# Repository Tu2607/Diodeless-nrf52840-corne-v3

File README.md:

# Diodeless nRF52840 Corne v3

A diodeless (direct-pin), Bluetooth variant of the [Corne Cherry v3.0.1](https://github.com/foostan/crkbd/tree/v3-final) by foostan. This repository holds the files and instructions needed to build one.

**Status: revision 0.4. The board passes KiCad DRC for connectivity and clearance, but it has not been fabricated or tested yet. Read [Check before ordering](#check-before-ordering) first.**

## What it is

- 3x6+3 keys per half, with the same outline, key positions and mounting holes as Corne v3
- nice!nano v2 (nRF52840) running ZMK, one per half
- One GPIO per switch and no diodes. All 21 GPIOs per half are used, including the three inner pads P1.01, P1.02 and P1.07
- Every key takes either a Kailh MX hotswap socket or a Kailh Choc v1 hotswap socket
- C&K GT11MSCBE sealed toggle as the power switch, where the Corne's TRRS jack was
- No OLED, no RGB and no TRRS cable

## 3D preview

These are renders of a 3D model built from the board file. Part positions and sizes are real, but the parts are simple block models and the socket heights are typical values, not measured.

For a model you can spin around, download [`3d-viewer.html`](3d-viewer.html) and open it in a browser. It needs an internet connection the first time, to load the 3D library.

The underside, with MX hotswap sockets on one half and Choc sockets on the other for comparison. A real build uses one type per key.

| MX sockets | Choc sockets |
|---|---|
|  |  |

## Files

| Path | Contents |
|---|---|
| `gerbers/corne-diodeless-gerbers.zip` | The file to upload to a PCB manufacturer |
| `gerbers/` | The same gerber and drill files, unzipped |
| `pcb/` | KiCad 7 board, project file and footprint library, for viewing or editing |
| `BOM.md` | Parts list with part numbers and quantities |
| `PINMAP.md` | Which pin each key uses |
| `boards/`, `config/`, `build.yaml`, `zephyr/` | ZMK firmware source. See [Firmware](#firmware) |
| `images/` | Board renders and 3D previews |
| `3d-viewer.html` | Interactive 3D model. Download it and open it in a browser |

There is no schematic. Each switch simply connects one controller pin to ground, as listed in `PINMAP.md`.

## Check before ordering

- **Power switch rating.** The GT11MSCBE is rated 0.4 VA at up to 20 V, about 95 mA at battery voltage. The nice!nano charges at about 100 mA through the switch, so the switch is at its limit while charging.
- **Inner controller pads.** The position of P1.01, P1.02 and P1.07 comes from community footprints. Check it against a real nice!nano on the 1:1 print.
- **Battery polarity.** JST-PH battery leads are not standardised. Match your battery's red wire to the + mark on the board.
- **Plates and cases.** Corne v3 plates and cases are cut for MX switches. A Choc build needs a Choc plate or no plate.

## Parts

The full parts list with part numbers and quantities is in [`BOM.md`](BOM.md).

## Ordering the PCB

Upload `gerbers/corne-diodeless-gerbers.zip`. It is a two-layer board, 1.6 mm thick. The file is a panel that holds both halves, so some manufacturers will price it as more than one design.

## Assembly

1. **Break the halves out** of the frame and file the tab edges smooth.
2. **Hotswap sockets, on the back.** Each key has two pairs of pads: the MX pair on one side of the switch centre and the Choc pair on the other. Solder sockets to one pair only. See the picture below.
3. **Power switch, on the top.** Solder the GT11MSCBE to the pads marked PWR at the inner edge. The three pads on one side are the contacts and the two on the other side hold it down. The pads match the land pattern in the C&K GT series datasheet (0.76 x 3.17 mm pads at 2.54 mm pitch, 8.38 mm across). The lever throws toward and away from the board edge.
4. **Reset button, on the top**, at the pads marked RESET.
5. **Battery connector, on the top**, at the pads marked BAT. Skip this if you will solder the battery leads straight to the pads.
6. **Controller sockets, on the top.** Fit the two 12-pin rows, and the three single sockets in the holes marked 107, 102 and 101.
7. **Controller.** Solder pins to the nice!nano, including the three inner pads, and plug it in face down, with the components toward the PCB and the USB port at the top edge.
8. **Battery.** With the power switch off, connect the battery, checking + and -.
9. **Switches and keycaps.**

### Using a different power switch

Two holes marked TOGGLE sit next to the power switch and are wired in parallel with it. To use an off-board switch, leave the PWR pads empty and wire your switch across those two holes.

## Firmware

The board runs [ZMK](https://zmk.dev). A stock Corne firmware will not work, because this board has no key matrix. This repo carries its own ZMK setup:

| Path | Contents |
|---|---|
| `boards/shields/corne_diodeless/` | The board definition: one pin per key for each half |
| `config/corne_diodeless.keymap` | The keymap. It starts as a copy of the stock ZMK Corne keymap |
| `config/corne_diodeless.conf` | Firmware settings |
| `build.yaml` | The list of firmware files to build |

### Getting the firmware

GitHub builds the firmware whenever the firmware files change. Open the repo's **Actions** tab, pick the latest "Build ZMK firmware" run, and download the `firmware` file at the bottom. It contains:

- `corne_diodeless_left-nice_nano_v2-zmk.uf2` for the left half
- `corne_diodeless_right-nice_nano_v2-zmk.uf2` for the right half
- `settings_reset-nice_nano_v2-zmk.uf2`, which clears saved Bluetooth pairings

### Flashing

1. Plug one half into USB.
2. Press its reset button twice quickly. A drive named NICENANO appears.
3. Copy that half's `.uf2` file onto the drive. The drive disappears when it is done.
4. Repeat for the other half.

The left half is the one that pairs with your computer. If the halves do not find each other, flash the settings reset file to both, then flash the normal files again.

### Changing the keymap

Fork this repo, edit `config/corne_diodeless.keymap`, and push. GitHub builds new firmware files for you. The [ZMK keymap documentation](https://zmk.dev/docs/keymaps) explains the format.

### First test

After flashing, press every key once to confirm all 21 pins on each half respond. A dead key on one of the three inner pads usually means that pin is not making contact. The firmware compiles but has not been tested on a real board yet.

## Power notes

- The switch disconnects the battery completely. With it off, the battery will not charge over USB.
- Turn the switch off before plugging or unplugging the battery.

## Licence and credit

Based on the Corne keyboard by foostan, used under the MIT licence. See `LICENSE`.

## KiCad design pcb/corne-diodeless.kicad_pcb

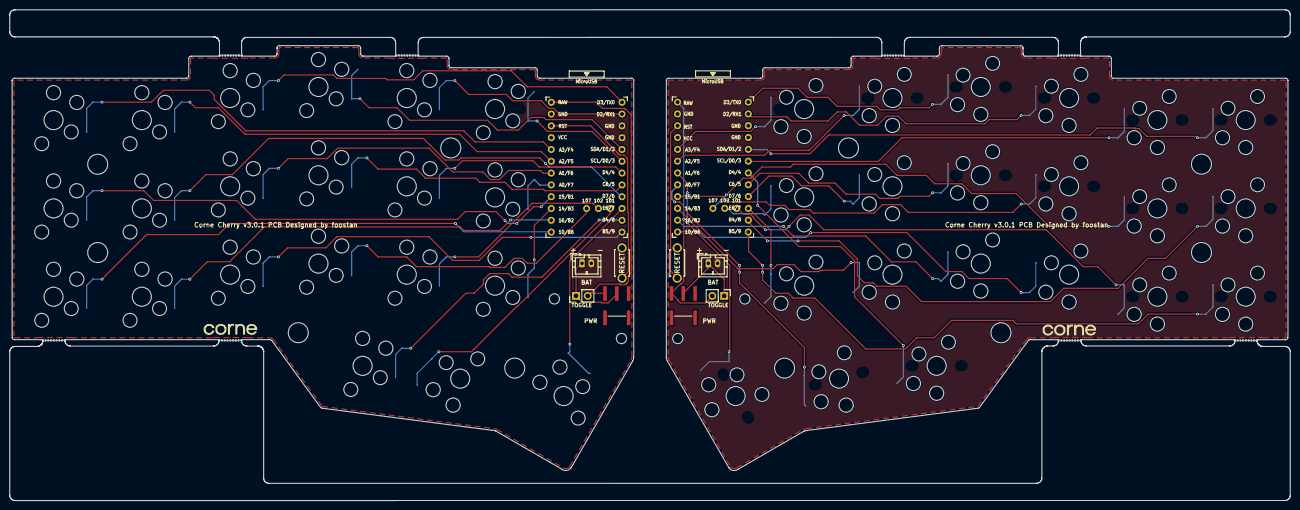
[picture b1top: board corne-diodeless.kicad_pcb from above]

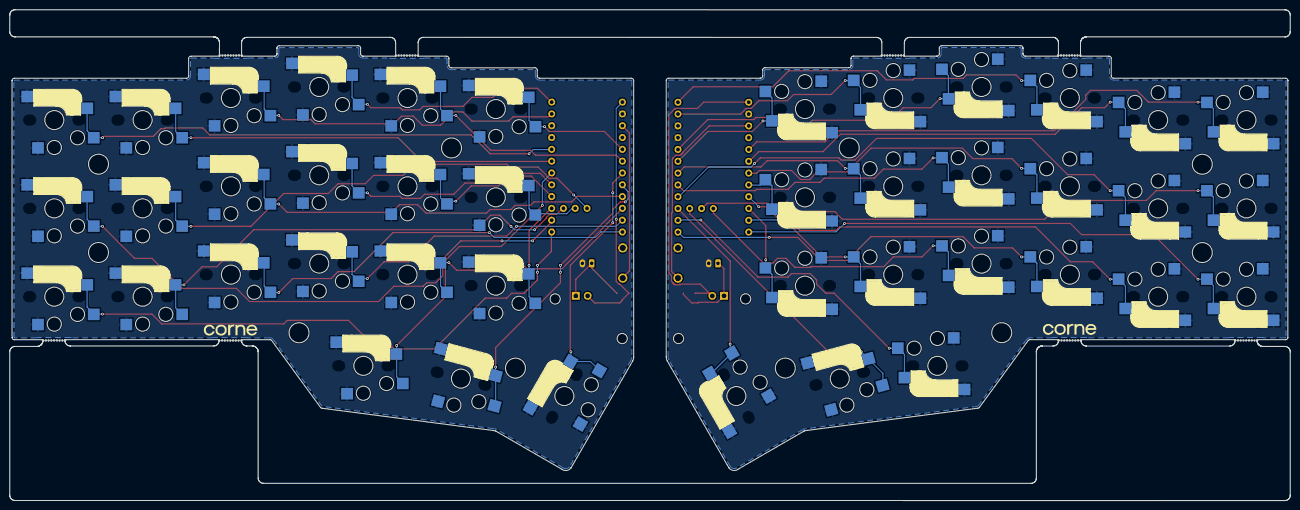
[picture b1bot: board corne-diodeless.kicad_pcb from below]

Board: 2 copper layers, 275.5 x 105.6 mm, 80 parts (9 on the bottom side), 50 nets.

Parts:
BT1, BT2: Battery JST-PH; JST_PH_B2B-PH-K_1x02_P2.00mm_Vertical
H1, H2, H3, H4, H5, H6, H7, H8, H9, H10, H11, H12, H13, H14: Val**; M2_HOLE_v2
J1, J2: nice!nano extra pins; nice_nano_extra_pins
J3, J4: Toggle wire pads; PinHeader_1x02_P2.54mm_Vertical
LOGO1, LOGO2, LOGO3, LOGO4: LOGO; corne-logo-horizontal
RSW1, RSW2: SW_PUSH; ResetSW_1side
SW1, SW2, SW3, SW4, SW5, SW6, SW7, SW8, SW9, SW10, SW11, SW12, SW13, SW14, SW15, SW16, SW17, SW18, SW19, SW20, SW22, SW23, SW24, SW25, SW26, SW27, SW28, SW29, SW30, SW31, SW32, SW33, SW34, SW35, SW36, SW37, SW38, SW39, SW40, SW41: SW_PUSH; CherryMX_Hotswap
SW21, SW42: SW_PUSH; CherryMX_Hotswap_1.5u
SW43, SW44: PWR GT11MSCBE; SW_SPDT_CK_GT11MSCBE
TAB1, TAB2, TAB3, TAB4, TAB5, TAB6, TAB7, TAB8: Breakaway_Tabs
U1, U2: ProMicro; ProMicro_v3

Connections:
BAT+: BT1.1, J3.1, SW43.2
BAT+_r: BT2.1, J4.1, SW44.2
GND: BT1.2, RSW1.2, SW1.2, SW2.2, SW3.2, SW4.2, SW5.2, SW6.2, SW7.2, SW8.2, SW9.2, SW10.2, SW11.2, SW12.2, SW13.2, SW14.2, SW15.2, SW16.2, SW17.2, SW18.2, SW19.2, SW20.2, SW21.2, U1.3, U1.4, U1.23
GND_r: BT2.2, RSW2.2, SW22.2, SW23.2, SW24.2, SW25.2, SW26.2, SW27.2, SW28.2, SW29.2, SW30.2, SW31.2, SW32.2, SW33.2, SW34.2, SW35.2, SW36.2, SW37.2, SW38.2, SW39.2, SW40.2, SW41.2, SW42.2, U2.3, U2.4, U2.23
K_R0C0: SW1.1, U1.20
K_R0C0_r: SW22.1, U2.5
K_R0C1: SW2.1, U1.19
K_R0C1_r: SW23.1, U2.6
K_R0C2: SW3.1, U1.1
K_R0C2_r: SW24.1, U2.2
K_R0C3: SW4.1, U1.5
K_R0C3_r: SW25.1, U2.1
K_R0C4: SW5.1, U1.2
K_R0C4_r: SW26.1, U2.19
K_R0C5: SW6.1, U1.6
K_R0C5_r: SW27.1, U2.20
K_R1C0: SW7.1, U1.16
K_R1C0_r: SW28.1, U2.11
K_R1C1: SW8.1, U1.9
K_R1C1_r: J2.P1.07, SW29.1
K_R1C2: SW9.1, U1.18
K_R1C2_r: SW30.1, U2.16
K_R1C3: SW10.1, U1.8
K_R1C3_r: SW31.1, U2.8
K_R1C4: SW11.1, U1.7
K_R1C4_r: SW32.1, U2.9
K_R1C5: SW12.1, U1.17
K_R1C5_r: J2.P1.02, SW33.1
K_R2C0: SW13.1, U1.13
K_R2C0_r: SW34.1, U2.12
K_R2C1: SW14.1, U1.14
K_R2C1_r: J2.P1.01, SW35.1
K_R2C2: SW15.1, U1.12
K_R2C2_r: SW36.1, U2.13
K_R2C3: J1.P1.07, SW16.1
K_R2C3_r: SW37.1, U2.14
K_R2C4: J1.P1.02, SW17.1
K_R2C4_r: SW38.1, U2.15
K_R2C5: SW18.1, U1.15
K_R2C5_r: SW39.1, U2.10
K_T0: SW19.1, U1.11
K_T0_r: SW40.1, U2.7
K_T1: J1.P1.01, SW20.1
K_T1_r: SW41.1, U2.17
K_T2: SW21.1, U1.10
K_T2_r: SW42.1, U2.18
RAW: J3.2, SW43.1, U1.24
RAW_r: J4.2, SW44.1, U2.24
RST: RSW1.1, U1.22
RST_r: RSW2.1, U2.22
